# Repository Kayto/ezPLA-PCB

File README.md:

# ezPLA

C64 PLA replacement based on Altera EPM7032 CPLD chip.

For more information check: https://ezcontents.org/commodore-64-pla-chip-replacement
Tests (includes video): https://ezcontents.org/commodore-64-custom-pla-chip-test

To load the custom symbols and footprints correctly you can edit the files: fp-lib-table and sym-lib-table and change the working directory before loading the project inside KiCad. Or (if you are using Windows) you can also place the project files inside: C:/Projects/KiCAD/ezPLA/

License: CC-BY-SA https://creativecommons.org/licenses/by-sa/4.0/

## Revision Status

Revision 2.0 - July 2023

**This fork by Kayto(@AdamT117) adds the CASRAM delay NAND gate to the PCB.**
[Tested working on a 250407 board.](https://twitter.com/AdamT117/status/1774082185294700785/photo/1)

### Jumper Settings

Solder Jumpers have been added to the back of the PCB to allow some element of control over the CASRAM delay, using up the remaining spare gates on the 74LS00.
Not sure this is really needed but provides greater flexibility (see below). 

The jumpers therefore allow the following;

**2 gate delay**

* JP1 - close label 2 pad to centre pad
* JP2 - close
* JP3 - open

**4 gate delay**
* JP1 - close label 4 pad to centre pad
* JP2 - open
* JP3 - close

### CASRAM delay
The [ezContents](https://ezcontents.org/troubleshooting-c64-pla-chip-replacement) blog provides a fantastic write up on the CASRAM delay.

The propagation delays of original PLAs are of the order of 25 ns ± 5 ns.

The CASRAM delay is introduced in the ezPLA by the switching delay within the added NAND gates - as the gates are inverting then the signal needs to be run through a pair of gates to remove the inversion.
According to the blog entry a 10ns delay was introduced using a pair of NAND gates of a 74LS00. This was versus a 3 to 15ns gate delay quoted in the data sheet - so looks to be around 5 ns per gate.

It is therefore anticipated that delays between 6 ns and 30 ns can be achieved with a 2 input quad NAND gate. The use of the extra gates introduced by the 4 gate jumpers is likely to reach a 20 ns delay.
Alternative NAND gates are also an option to control the delay, albeit a bit trial and error. For example the SN7438 quotes typical gate delays of 11 ns to 14 ns.

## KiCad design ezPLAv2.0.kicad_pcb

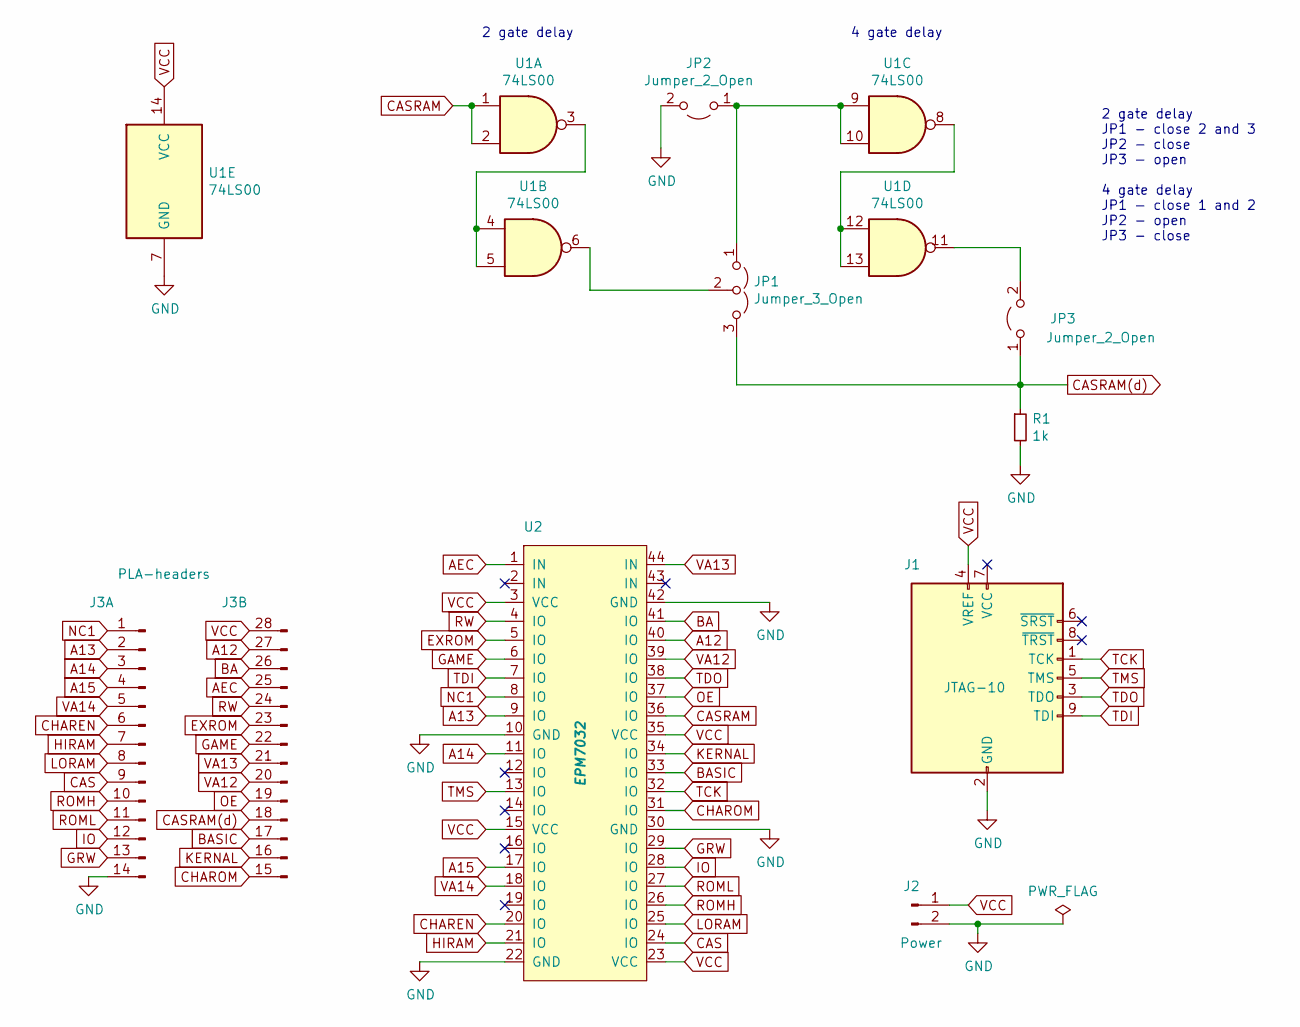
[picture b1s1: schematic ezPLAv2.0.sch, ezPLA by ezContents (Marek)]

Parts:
J1: JTAG-10; PinHeader_2x05_P2.54mm_Vertical
J2: Power; PinHeader_1x02_P2.54mm_Vertical
J3: PLA-headers; DIP-28_W15.24mm_mirrored
JP1: Jumper_3_Open; SolderJumper-3_P1.3mm_Open_Pad1.0x1.5mm_NumberLabels
JP2, JP3: Jumper_2_Open; SolderJumper-2_P1.3mm_Open_Pad1.0x1.5mm
R1: 1k; R_Axial_DIN0207_L6.3mm_D2.5mm_P7.62mm_Horizontal
U1: 74LS00; DIP-14_W7.62mm
U2: EPM7032; PLCC-44_THT-Socket

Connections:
A12: J3.27, U2.40 (IO)
A13: J3.2, U2.9 (IO)
A14: J3.3, U2.11 (IO)
A15: J3.4, U2.17 (IO)
AEC: J3.25, U2.1 (IN)
BA: J3.26, U2.41 (IO)
BASIC: J3.17, U2.33 (IO)
CAS: J3.9, U2.24 (IO)
CASRAM: U1.1, U1.2, U2.36 (IO)
CASRAM(d): J3.18, JP1.3 (B), JP3.1 (A), R1.1
CHAREN: J3.6, U2.20 (IO)
CHAROM: J3.15, U2.31 (IO)
EXROM: J3.23, U2.5 (IO)
GAME: J3.22, U2.6 (IO)
GND: J1.2 (GND), J1.10 (GND), J2.2, J3.14, JP2.2 (B), R1.2, U1.7 (GND), U2.10 (GND), U2.22 (GND), U2.30 (GND), U2.42 (GND)
GRW: J3.13, U2.29 (IO)
HIRAM: J3.7, U2.21 (IO)
IO: J3.12, U2.28 (IO)
KERNAL: J3.16, U2.34 (IO)
LORAM: J3.8, U2.25 (IO)
NC1: J3.1, U2.8 (IO)
unnamed: JP1.1 (A), JP2.1 (A), U1.9, U1.10
unnamed: JP1.2 (C), U1.6
unnamed: JP3.2 (B), U1.11
unnamed: U1.3, U1.4, U1.5
unnamed: U1.8, U1.12, U1.13
OE: J3.19, U2.37 (IO)
ROMH: J3.10, U2.26 (IO)
ROML: J3.11, U2.27 (IO)
RW: J3.24, U2.4 (IO)
TCK: J1.1 (TCK), U2.32 (IO)
TDI: J1.9 (TDI), U2.7 (IO)
TDO: J1.3 (TDO), U2.38 (IO)
TMS: J1.5 (TMS), U2.13 (IO)
VA12: J3.20, U2.39 (IO)
VA13: J3.21, U2.44 (IN)
VA14: J3.5, U2.18 (IO)
VCC: J1.4 (VREF), J2.1, J3.28, U1.14 (VCC), U2.3 (VCC), U2.15 (VCC), U2.23 (VCC), U2.35 (VCC)

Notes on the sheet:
2 gate delay
4 gate delay
2 gate delay JP1 - close 2 and 3 JP2 - close JP3 - open 4 gate delay JP1 - close 1 and 2 JP2 - open JP3 - close

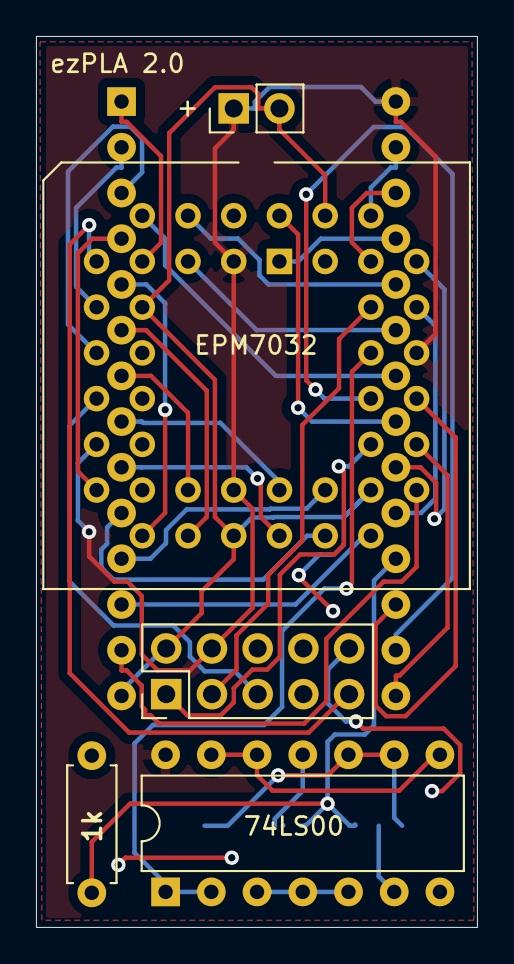
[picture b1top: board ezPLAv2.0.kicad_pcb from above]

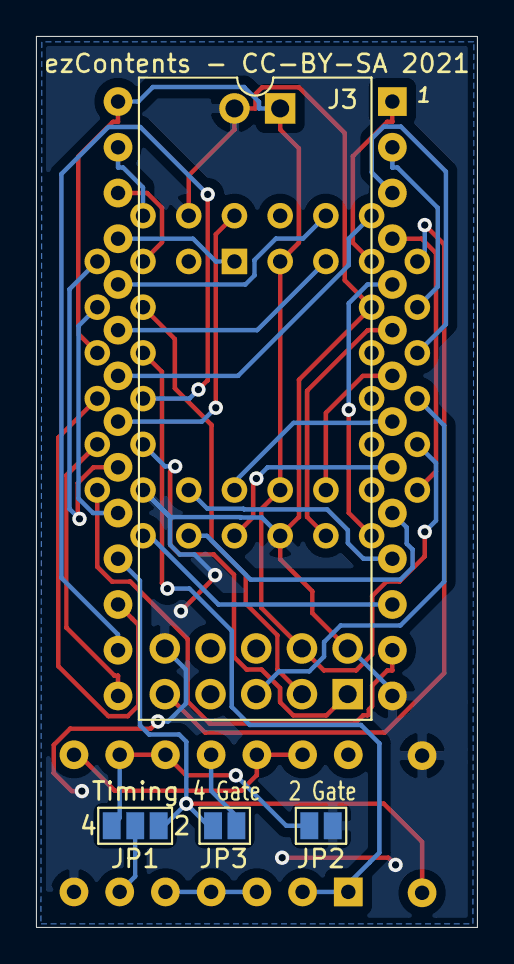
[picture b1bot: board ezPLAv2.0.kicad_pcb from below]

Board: 2 copper layers, 24.5 x 49.5 mm, 9 parts (4 on the bottom side), 38 nets.

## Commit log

2023-07-11 rev2.0 PCB with NAND Gate CASRAM delay
2023-07-22 jumpers added
2023-07-24 Test PCB added
2024-03-30 Update README.md
    removed test board
2024-03-30 Test board removed

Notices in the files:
ezPLAv2.0.kicad_pcb:
ezContents - CC-BY-SA 2021
